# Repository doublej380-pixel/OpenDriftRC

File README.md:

OpenDrift is an open source drift gyro for RC drift cars, built around the Waveshare ESP32-S3 Touch AMOLED 1.64 board. It reads steering, throttle, and optional gain channels from a receiver, mixes driver steering with gyro correction, outputs steering and optional throttle signals, and exposes tuning through both the onboard touch UI and a WiFi web configurator.

OpenDrift v1.0 uses a dedicated selectable-rate control task, a single gyro filter, continuous yaw prediction, throttle-informed load-change prediction, and non-accumulating quiet-drift reference feedback. The goal is to make gyro setup less of a black box while keeping the active control path small enough to reason about.

See the current [Technical Tuning Reference](OpenDrift/docs/Tuning.md) for the setup order, symptom table, surface-profile workflow, and findings from real track testing. The public [tuning guide](https://opendriftrc.com/tuning/) provides the shorter trackside workflow.

Developers and AI assistants can start with the
[project context and handoff](OpenDrift/docs/PROJECT_CONTEXT.md), covering the
development history, architecture, validated findings, safety constraints,
current local work, and deferred investigations. It is a dated summary, not
a verbatim chat archive; verify it against the current source.

## Install Firmware

Visit [opendriftrc.com](https://opendriftrc.com) for the project overview, [wiring reference](https://opendriftrc.com/wiring/), and Open Beta firmware. The [browser installer](https://opendriftrc.com/flash/) provides current AMOLED images with either PWM or CRSF receiver support, without an account, source compilation, or command-line tools. Historical round-display releases remain available but are frozen.

## Current Features

- ESP32-S3 firmware using PlatformIO and Arduino.
- 280 x 456 AMOLED touch UI with swipeable pages and a permanent built-in
  background fallback.
- Up to 16 persistent custom AMOLED backgrounds, selectable from the display
  or web configurator. JPG, PNG, and WebP images can be converted locally at
  [opendriftrc.com/backgrounds](https://opendriftrc.com/backgrounds/).
- Persistent AMOLED theme engine with light/dark text, seven accent palettes,
  and background-aware translucent control panels, based on work contributed
  by [J3vb](https://github.com/J3vb).
- Dedicated 333 Hz IMU/control/steering task isolated from UI, WiFi, and logging work.
- Continuous yaw-acceleration prediction with throttle-informed look-ahead.
- Quiet-drift reference feedback that yields to driver steering and throttle changes.
- Receiver steering input.
- Optional receiver throttle sensing with automatic Performance Mode behavior.
- Receiver gyro gain input.
- Selectable GPIO 18 gyro-gain input or throttle passthrough output.
- Servo output with center, reverse, and travel settings.
- Physical servo endpoint calibration for max left, center, and max right.
- Separate radio steering travel limit.
- Separate servo reverse and gyro reverse.
- Gyro tuning:
  - gain
  - deadband
  - maximum correction
  - smoothing
  - Prediction
  - Countersteer Assist
  - Transition Speed
  - Driver Priority
  - Anti Wobble
- Up to 12 persistent named surface/driving profiles.
- Scrollable trackside profile selection on both displays.
- Do-nothing signal-loss behavior when steering input is lost.
- WiFi access point.
- Browser-based web configurator.
- Non-blocking PSRAM blackbox logging with controller, prediction, throttle, notch, chassis-motion, and correction telemetry.
- Parked blackbox archiving to sequential CSV files on AMOLED microSD, with an
  internal-flash fallback when no card is installed.
- Persistent settings stored in ESP32 preferences.
- Transition Speed adjustment centered at the neutral baseline of `50`.
- Driver Priority adjustment that yields fast direct gyro gain as steering input increases; default `0` preserves the established response.
- Phase-aware Anti Wobble notch with a track-tested default of `50`.
- Separate PWM and full-duplex CRSF targets for Waveshare AMOLED V1 and V2.
- Full-duplex CRSF steering, throttle, gain, link statistics, parameter
  telemetry, neutral failsafes, and [EdgeTX tuning](https://github.com/doublej380-pixel/OpenDriftRC/releases/download/v1.0.8/OpenDrift.lua).
- CRSF channel routing to accessory PWM outputs: GPIO 1–8 on AMOLED V1 and
  GPIO 3–8 on AMOLED V2.

## Hardware Routing

### Supported Boards

The **Waveshare ESP32-S3 Touch AMOLED 1.64** is the final and primary OpenDrift hardware target. New development, UI work, and release testing target this board.

Waveshare ships V1 and V2 revisions that require different firmware. V1 has its version silkscreen at the top of the PCB and uses LCD_CS on GPIO 9. V2 has the silkscreen beside the right-side pin headers and uses LCD_CS on GPIO 46. Select the exact revision in the web flasher.

The older Waveshare 1.28-inch round display build is deprecated and frozen. Its PlatformIO environment and implementation remain in the repository for experimentation, but no new firmware releases or feature-parity work are planned.

AMOLED V1 and the Round board use this PWM pinout:

| Signal | GPIO | Direction | Notes |
| --- | ---: | --- | --- |
| Receiver steering / servo in | 15 | Input | Standard RC PWM input |
| Receiver throttle / throttle in | 16 | Input | Throttle sensing and blackbox input |
| Steering servo / servo out | 17 | Output | Stabilized steering command |
| Gain input / throttle output | 18 | Selectable | Gain-channel input by default, or throttle passthrough output |

GPIO 18 cannot provide throttle output and read receiver gain at the same time.
To keep throttle sensing and gain adjustment, split the receiver throttle
signal to GPIO 16 and the ESC rather than plugging the ESC into OpenDrift.

Make sure the receiver, ESP32 board, and servo power system share ground.

AMOLED V2 keeps receiver steering on GPIO 15 and throttle on GPIO 16, but moves steering output to GPIO 1 and the switchable gain/throttle connection to GPIO 2. Do not use GPIO 17/18 for OpenDrift signals on V2; Waveshare connects those pins to IMU_INT2 and TP_INT.

CRSF targets repurpose the receiver pins:

| Signal | GPIO | Direction | Notes |
| --- | ---: | --- | --- |
| CRSF receiver TX | 17 | Input | Native CRSF channel and link frames |
| CRSF receiver RX | 18 | Output | Full-duplex parameter telemetry |
| Steering servo / servo port | 15 | Output | Fixed 333 Hz servo PWM |
| ESC throttle / throttle port | 16 | Output | Standard 50 Hz ESC PWM with active-neutral failsafe |

AMOLED V2 instead uses GPIO 1 for CRSF RX and GPIO 2 for CRSF TX while retaining GPIO 15 steering-servo output and GPIO 16 ESC output. All CRSF targets use the same full-duplex implementation and the
separate `OpenDriftCRSF` settings namespace and do not overwrite a PWM tune.

CRSF builds can also mirror any receiver channel to accessory outputs from the
WiFi web configurator. AMOLED V1 exposes GPIO 1–8; AMOLED V2 exposes GPIO 3–8
because GPIO 1/2 carry CRSF. Each enabled pin emits standard 50 Hz receiver PWM
and returns to 1500 microseconds when the CRSF link is lost. These are 3.3 V
signal outputs only: power lights and accessories separately and share ground.

Throttle sensing is not required for basic stabilization, but it is strongly recommended. With the throttle signal connected, OpenDrift can release settled-drift features during power changes instead of inferring those events from yaw alone. Treat it like a sensored-motor cable: the fallback works without it, while Performance Mode has substantially better phase awareness.

The servo should be powered from a suitable BEC or ESC receiver rail. Do not rely on the ESP32 board to power a steering servo. A DIY installation must feed the display/development board regulated 5 V, never an unregulated or 6 V-plus BEC output. The OpenDrift daughter boards under development include an onboard regulator. ESP32-S3 GPIOs are 3.3 V signal pins and are not 5 V tolerant.

## Build And Upload

The firmware project is in:

`OpenDrift/`

## Custom AMOLED Backgrounds

OpenDrift keeps the built-in galaxy image in firmware and can additionally
store up to 16 user backgrounds in the board's FFat partition. Custom images
must be 456 x 280 raw RGB565 files; the browser-based
[background converter](https://opendriftrc.com/backgrounds/) creates the exact
format locally from JPG, PNG, or WebP files.

To install one, join the gyro's `OpenDrift` WiFi network, open
`http://192.168.4.1`, and use the **AMOLED Backgrounds** card. Uploaded images
can be selected or deleted there, and can also be selected from the
**Backgrounds** page on the AMOLED display. Keep the car stationary while an
image is being written to flash. Leaving the selection on **Built-in** uses the
factory background and consumes no additional storage.

Build with PlatformIO:

```sh
pio run
```

The default environment is `waveshare_amoled_164`. Build or upload it explicitly with:

```sh
pio run -e waveshare_amoled_164
pio run -e waveshare_amoled_164 -t upload
```

The custom PlatformIO board definition is included at `OpenDrift/boards/waveshare_amoled_164.json`.

AMOLED V2 uses separate targets:

```sh
pio run -e waveshare_amoled_164_v2
pio run -e waveshare_amoled_164_v2_crsf
```

CRSF builds are intentionally separate:

```sh
pio run -e waveshare_amoled_164_crsf
```

Both supported targets enable full-duplex CRSF, GPIO 16 ESC output, and neutral-hold arming. Telemetry uses GPIO 18 on AMOLED V1 and GPIO 2 on AMOLED V2.

Main dependencies are managed in `OpenDrift/platformio.ini`:

- SensorLib
- LovyanGFX
- ESP32Servo

## First Power-On

On boot, OpenDrift initializes:

1. Display
2. Settings
3. IMU
4. Servo output
5. Receiver inputs
6. Touch
7. Gyro calibration
8. WiFi, if enabled
9. UI

Keep the car still during startup so gyro calibration can capture a clean yaw-rate offset.

## Onboard UI Pages

Swipe left/right to move between pages.

### Main

Shows the current gyro gain and provides:

- `- / +`: adjust stored gain when radio gain input is not overriding it.
- `CAL`: recalibrate gyro offset. Use this when the car is sitting still and the gyro seems biased.

### Core

Primary correction limits:

- `Deadband`: yaw-rate zone ignored around zero.
- `MAX CORRECTION`: maximum gyro movement across the full calibrated endpoint-to-endpoint steering span. `50%` equals center-to-endpoint authority; `100%` can override one endpoint to the other.
- `GYRO REV`: reverses only the gyro correction direction.

Use `GYRO REV` when normal steering direction is correct, but the gyro counter-steers the wrong way.

### Response

Fast controller behavior:

- `SMOOTHING`: the optional software yaw low-pass; defaults to `0.00` (bypass).
- QMI8658 gyro hardware LPF is bypassed; its selector is retired.
- `PREDICTION`: continuous yaw-acceleration look-ahead.

### Assistance

Slow quiet-drift behavior:

- `COUNTERSTEER`: chooses how much additional steady countersteer OpenDrift carries. Zero preserves the driver-led base response; higher values reduce the steering load on the driver without increasing fast yaw damping.
Hold Assist, Drift Memory, and Memory Limit are retired on non-MPU6050 builds.
Old saved values and profiles cannot reactivate them. The experimental MPU6050
targets retain their original controls, defaults, and 20/98/256 Hz filter choices.

### Tail Response

`TAIL SPEED` is tuned separately from the core v1.0 controls:

- `50` is the Open Beta baseline response.
- Below `50` adds damping during deliberate entries and transitions.
- Above `50` releases some damping so the chassis can rotate faster.
- The effect is reduced in a settled drift and cannot reverse gyro correction.

Keep it at `50` unless deliberately collecting same-car experimental A/B data.

`SMOOTH` is intentionally inverted from raw filter math: higher numbers mean more smoothing and slower gyro response.

Deadband is applied as a soft deadband. Small yaw noise is still ignored, but correction fades in from zero instead of jumping as soon as yaw crosses the deadband value.

Conservative first-power values:

| Setting | Start |
| --- | ---: |
| Gain | 1.50 |
| Deadband | 4.0 |
| Max correction | 100% |
| Smoothing | 0.00 |
| Countersteer Assist | 100 |
| Driver Priority | 0 |
| Prediction | 0 |

Tune symptoms:

| Symptom | Try |
| --- | --- |
| Weaves left/right driving straight | Increase deadband or lower gain |
| Initial response is strong but runs out of authority | Raise Max Correction carefully |
| Fast response overshoots | Add Prediction in steps of 5 |
| Prediction makes transitions nervous | Lower Prediction |
| Car is stable but the driver carries too much countersteer | Raise Countersteer Assist in steps of 10 |
| Gyro feels too hands-on during a settled drift | Lower Countersteer Assist |
| High gain feels restrictive near full steering | Add Driver Priority in steps of 5; start below 20 |
| Mid-drift wheel oscillation | Lower gain first; verify servo and chassis |
| Feels slow or lazy | Lower smoothing slightly or raise gain |

### Radio

Live receiver monitor:

- Steering pulse and signal state.
- Gain pulse and signal state.
- Current gain value.
- Calibration values.
- Position bars for steering and gain.

Use this page to confirm the receiver is connected and moving through a sensible range.

In a CRSF build the monitor shows channel 1 steering, channel 2 throttle, and
channel 3 gain decoded from the digital link.

### Steering

Steering output setup:

- `TRV`: scales driver steering input without reducing gyro correction authority.
- `REV`: reverses physical servo direction.
- Swipe once more to open the dedicated **Physical Endpoints** page.

### Physical Servo Endpoints

The calibration page uses three large capture buttons. Each button starts red
and turns green after it has captured the servo's actual physical PWM position:

- `MAX LEFT`: position the wheels at their safe physical left stop, then capture it.
- `CENTER`: capture the transmitter at neutral.
- `MAX RIGHT`: position the wheels at their safe physical right stop, then capture it.

OpenDrift saves the calibration after all three physical positions are captured
on opposite sides of center. The saved endpoints become the final asymmetric
servo map and hard clamp, so neither the driver nor gyro can push through them.

CRSF users can perform the same three captures from the EdgeTX `OpenDrift.lua`
tool. Calibration state is persistent and shared: completing it on the radio
turns the AMOLED buttons green, while completing it on the display updates the
radio's `Endpoints` status to `YES`.

Suggested calibration flow:

1. Set servo direction first, then use steering/transmitter endpoint adjustment to position the wheels at the safe physical left stop and tap `MAX LEFT`.
2. Release steering to neutral and tap `CENTER`.
3. Position the wheels at the safe physical right stop and tap `MAX RIGHT`.
4. Confirm all three buttons are green and the page says `SAVED - TAP TO RESET`.
5. Return to Steering and verify the wheels remain inside both saved physical stops.

Changing `REV`, Servo Center, or Servo Travel after calibration deliberately
clears the saved calibration because those changes alter the physical output map.

Servo reverse and gyro reverse are separate on purpose:

- Use `REV` on the Steering page when driver steering moves the wheels backward.
- Use `GYRO REV` on the Gyro page when driver steering is correct but gyro correction is backward.

Physical endpoint calibration and steering travel are separate on purpose:

- Use `MAX LEFT`, `CENTER`, and `MAX RIGHT` to set the servo's physical output limits.
- Use `TRV` to scale driver steering without reducing gyro authority.
- Use Max Correction to select how much of the calibrated physical range the gyro may command.

### WiFi

Shows WiFi state and connected client count.

AMOLED development builds default to **WiFi off** on fresh installs and factory
reset. Turn it on from this page when needed. Existing saved boot preferences
are preserved; change "Enable WiFi on boot" in the web configurator if desired.
When off, the radio driver is stopped/deinitialized, mDNS is stopped, and the
HTTP client/listener closes. Health checks and HTTP request polling do not run.
The small route table and shared networking framework allocations can remain
in memory; "off" does not mean the firmware has zero networking-related RAM.

- `WIFI ON/OFF`: toggles the access point.

When WiFi is enabled, connect to the `OpenDrift` network and open:

`http://192.168.4.1/`

### System

Basic firmware/system information. Tap the GPIO 18 mode button to switch between `GAIN INPUT` and `THROTTLE OUT`.

### Profiles

The Profiles page lists the driving profiles created in the web configurator. Tap a profile to activate its complete driving tune. Swipe vertically when more than four profiles exist; the list supports up to 12 profiles.

Profiles save gain, deadband, max correction, smoothing, Prediction, Countersteer Assist, Driver Priority, and radio steering travel. Retired fields remain reserved for compatibility but are forced off on non-MPU6050 builds. Trackside adjustments automatically save back to the active profile.

Hardware and installation settings remain global, including gyro/servo direction, physical steering endpoints, servo center and travel, WiFi, logging, and GPIO mode. Switching surfaces therefore cannot disturb the car's physical setup.

### Control and servo rate

Current development firmware uses **333 Hz only** for steering/control, with an approximately 3 ms interval. **Use only a servo explicitly rated for 333 Hz.** Digital does not automatically mean compatible; an unsupported update rate can cause heat, buzzing, erratic steering, or servo damage. Existing 250 Hz settings migrate to 333 Hz on installation.

The screen and web configurator show the fixed rate; there is no rate selector in the radio menu. Throttle output retains its independent 50/250/333 Hz setting and is not forced to the steering rate.

## Web Configurator

When WiFi is enabled, OpenDrift starts a web configurator at:

`http://192.168.4.1/`

Current web settings:

- Create named driving profiles from the current tune
- Activate or delete existing profiles
- Gyro gain
- Channel 3 gain minimum / maximum (`0.00-6.00`)
- Deadband
- Reverse gyro correction
- Max correction
- Smoothing
- Prediction strength
- Transition Speed
- Driver Priority
- Anti Wobble
- Servo reverse
- Servo center
- Servo travel
- Steering max left / center / max right
- Radio steering travel
- Gain channel low / high
- GPIO 18 gain-input or throttle-output mode
- WiFi enabled on boot
- WiFi auto-off timeout
- Blackbox logging enabled
- Raw pitch, roll, acceleration, and surface-disturbance telemetry for chassis analysis

The web page also shows the active profile, live receiver pulse values for steering, throttle, and gain, plus the active GPIO 18 mode.

Use the web configurator when you want to make several changes quickly. Use the onboard UI when tuning trackside without a phone or laptop.

## Onboard Blackbox Log

OpenDrift records fixed-size blackbox samples into a 4 MB circular PSRAM buffer at about 20 Hz while steering receiver signal is present.

Blackbox logging is disabled by default. Enable `Onboard logging` in the web configurator only when you want to collect data, then save settings.

No flash or filesystem writes occur while driving. Once the circular buffer is
full, the oldest records are overwritten so the newest behavior remains
available. Park the car before saving the RAM log to persistent storage.

On AMOLED hardware, an installed microSD card is preferred and each dump is
saved as a new CSV (`opendrift-blackbox-0001.csv`, `0002`, and onward). Existing
sessions are preserved and numbering continues after reboot. Without an SD
card, OpenDrift stores one compact binary archive in internal flash and converts
it to CSV when downloaded through the web configurator.

The dedicated AMOLED **Blackbox** page shows the current RAM records, used and
available space, captured duration, archive destination, saved-log statistics,
and dump progress. It also provides logging, dump, and RAM-clear controls.

For acquisition/wobble testing, the web configurator's **Control diagnostics**
card captures up to 45 seconds at control-loop rate. Start it before driving.
With an SD card, the ordinary dump action also saves a matching numbered
`opendrift-diagnostics-0001.csv` beside the blackbox CSV. Wait until dump
completion before powering off. Without SD, download the timing CSV over WiFi
before restarting; internal-flash dumps do not include this RAM-only capture.
See [IMU diagnostics](OpenDrift/docs/IMU_DIAGNOSTICS.md) and
[screen performance testing](OpenDrift/docs/SCREEN_PERFORMANCE.md).

### AMOLED USB maintenance and boot recovery

All AMOLED V1/V2 PWM/CRSF builds, including the private GPIO8 target, support
USB maintenance. **No SD card is required for firmware updates.** Hold **USB
MODE** on the System page for 1.5 seconds while parked. The board restarts into
an isolated mode with steering, throttle, and controller tasks inactive.
Connect a data-capable USB cable and copy the correct build's application
`firmware.bin` onto the firmware-update drive. Wait for **Update Complete**
and automatic reboot; do not disconnect during writing. An inserted SD card
appears separately as a read-only log drive. The maintenance restart button
disconnects the volumes before returning to normal operation.

The SD-ready indication reports device-side readiness, not completion of the
computer's filesystem mount. USB SD reads now use up to the existing 4 KB
buffer with event-driven completion instead of per-sector polling. See
[USB SD performance testing](OpenDrift/docs/USB_SD_PERFORMANCE.md) if the
drive appears but takes a long time to open; hardware validation is still
required to measure the improvement.

For official builds previously using the single-app partition layout, install
the full factory image once through the webflasher or perform a normal full
PlatformIO upload: an app-only USB update
cannot install a new partition table. The new layout keeps NVS and FFat at
their existing addresses, but back up your tune/logs before upgrading. USB
serial ports may re-enumerate after the switch to native TinyUSB. Do not erase
the whole chip as part of the normal upgrade.

After three consecutive unfinished boots across software/watchdog resets,
the next boot enters USB recovery before the IMU, outputs, and controller are
started. Automatic recovery skips SD mounting so a bad card cannot block the
updater. Successful normal startup clears the RTC failure audit after 15
seconds. Intentional USB-mode changes are excluded. Cold power loss/brownout
starts a fresh audit; corrupt apps/bootloaders still require hardware BOOT
recovery. The headless private Matrix builds retain their existing USB serial
configuration; this AMOLED maintenance interface is not enabled on Matrix.

The web configurator shows the current log size and provides:

- `Download CSV`
- `Clear RAM Log`
- `Dump RAM Log to SD card` or internal flash, according to available storage
- `Download saved CSV`

Log rows include:

- Time
- Raw yaw rate
- Filtered yaw rate
- Roll and pitch gyro rates (`gyro_x_dps`, `gyro_y_dps`)
- Raw X/Y/Z acceleration in g
- Total acceleration magnitude and high-frequency acceleration delta
- A filtered `surface_disturbance` score from `0.0` to `1.0`
- Requested gyro correction before Max Correction
- Limited gyro correction after Max Correction
- Applied gyro correction after the driver/gyro steering mix
- Correction saturation state
- Steering input and calibrated steering command
- Servo output
- Reserved Servo Quiet field (zero; command suppression is retired)
- Throttle input
- Gain input and active gain
- Active deadband, max correction, smoothing, Prediction, Countersteer Assist, and Driver Priority (retired memory/hold fields remain zero for CSV compatibility)
- Driver Priority scale and effective live direct gain
- Predicted yaw, quiet-drift reference, reference error, steady countersteer contribution, and memory correction
- Driver steering activity and throttle-prediction blend
- Controller phase (`0` idle, `1` entry, `2` settled, `3` transition) and reference-lock blend
- Anti Wobble notch depth, isolated residual, tracked notch frequency, transition-authority blend, and throttle-lift blend
- Steering/throttle/gain signal state and GPIO 18 mode

Suggested test workflow:

1. Connect to the `OpenDrift` WiFi network.
2. Open `http://192.168.4.1/`.
3. Enable onboard logging if it is off, then save settings.
4. Tap `Clear RAM Log`.
5. Drive the car.
6. Stop and leave the car parked for two seconds.
7. Dump the RAM log from the AMOLED Blackbox page, EdgeTX tool, or web
   configurator.
8. Download the saved CSV over WiFi, or remove/read the SD card later.

The CSV can be pasted into a spreadsheet or plotted to see whether the car spun because of delayed correction, overcorrection, max correction saturation, noisy yaw, or steering/radio behavior.

`surface_disturbance` still combines sudden acceleration-vector changes, roll/pitch rate, and low-g unloading indicators for analysis. OpenDrift v1.0 logs it but does not currently apply terrain correction.

## Gyro Algorithm Overview

Current development firmware runs this path at the fixed 333 Hz rate:

1. Read receiver steering, throttle, and IMU yaw.
2. Subtract calibrated gyro offset and apply soft deadband.
3. Bypass QMI gyro hardware LPF and apply optional software yaw low-pass.
4. Estimate short-horizon yaw from filtered yaw acceleration.
5. Extend that horizon when throttle predicts application or a longer off-throttle load change.
6. Shape damping briefly during deliberate direction changes without changing the hard correction ceiling.
7. Apply the phase-aware Anti Wobble notch around the tracked 2.5-3.6 Hz wheel-resonance band while preserving slow chassis yaw and useful response outside that band.
8. Convert predicted yaw directly into correction with Gain.
9. Learn a slow yaw reference while driver steering and throttle are quiet.
10. Add optional Countersteer Assist from the slow learned reference only.
11. Limit signed gyro movement to the configured full-span Max Correction
    percentage, then mix it with driver steering and clamp the combined command.
12. Apply the calibrated physical endpoint map as the final hard servo limit.

Driver steering activity and throttle changes make the slow reference yield
immediately. Neither disables the fast direct damping path.

## Signal Loss Behavior

Current CRSF development builds also require [CH4 arming](OpenDrift/docs/ARMING.md).
CH4 low holds steering centered and throttle neutral with the screen usable;
CH4 high requests drive after a neutral hold and sleeps the AMOLED/UI. Physical
endpoint capture/reset is unavailable under the selected strict parked lock.
Read the bench checklist before installing this development firmware.

The standard PWM builds retain the existing do-nothing behavior: if steering
input disappears, OpenDrift does not send a new servo command.

This leaves the servo at the last commanded position. It is intentionally a simple do-nothing behavior while failsafe strategy is still being evaluated.

The full CRSF build has deterministic behavior because all channels share one
link state. A channel frame older than 50 ms centers steering and commands
neutral throttle. Throttle remains locked until a valid link has held neutral
for 500 ms after boot or reconnection.

## Tuning

Use the [Technical Tuning Reference](OpenDrift/docs/Tuning.md) rather than tuning every setting at once. The most important lessons from development are:

- Establish a mechanically sound car before blaming the gyro.
- Set the servo's internal anti-wobble only as high as it can run without buzzing; high servo torque/power can amplify internal oscillation.
- Treat Gain as the primary surface-dependent setting and store each surface in a profile.
- Tune entries with Gain, Max Correction, and optional Smoothing.
- Add Prediction in small steps only after the direct response is understood.
- Use Countersteer Assist to choose driver-led versus gyro-led settled drifts without retuning Gain.
- Connect throttle sensing so OpenDrift can anticipate power and load changes.

OpenDrift v1.0 is the first public controller. Start from the conservative
values in the tuning reference and save proven surface setups as profiles.

## Future Work

- **Servo resonance calibration:** add a stationary calibration mode that sweeps a small steering command across a safe frequency range and captures high-rate chassis IMU data. Because the servo is rigidly mounted to the chassis, its buzz and self-oscillation should be measurable without another sensor. The first version should compare vibration energy, dominant resonances, settling, and left/right behavior to help evaluate internal servo anti-wobble, torque, power, and response settings and recommend OpenDrift quiet-band and correction-rate settings. Command shaping or resonance compensation should only follow after repeatable measurements show that it can reduce vibration without adding harmful control-loop delay.

## Project Layout

Important folders:

- `OpenDrift/src/main.cpp`: main firmware loop and control mixing.
- `OpenDrift/lib/GyroController`: gyro filtering and correction generation.
- `OpenDrift/lib/RadioInput`: receiver PWM input capture.
- `OpenDrift/lib/CrsfInput`: bounded native CRSF frame decoding and telemetry.
- `OpenDrift/lib/CrsfParameterDevice`: bidirectional CRSF settings device.
- `OpenDrift/lib/EscOutput`: dedicated 50 Hz LEDC throttle output.
- `OpenDrift/lib/Servo`: servo output wrapper.
- `OpenDrift/lib/Settings`: persistent settings.
- `OpenDrift/lib/UI`: onboard touch UI.
- `OpenDrift/lib/WebConfigurator`: web settings page.
- `OpenDrift/lib/WIFIManager`: WiFi access point control.
- `OpenDrift/lib/Backgrounds`: persistent AMOLED background storage and
  recovery.
- `OpenDrift/docs/Tuning.md`: complete tuning and blackbox interpretation guide.
- `OpenDrift/docs/CRSF-Experimental.md`: CRSF wiring, failsafes, and validation
  workflow.
- `OpenDrift/radio/edgetx`: source for the [OpenDrift EdgeTX tuning tool](https://github.com/doublej380-pixel/OpenDriftRC/releases/download/v1.0.8/OpenDrift.lua).
- `OpenDrift/assets/backgrounds`: built-in AMOLED fallback background data.
- `OpenDrift/boards`: custom PlatformIO board definitions.

## License

See `LICENSE`.

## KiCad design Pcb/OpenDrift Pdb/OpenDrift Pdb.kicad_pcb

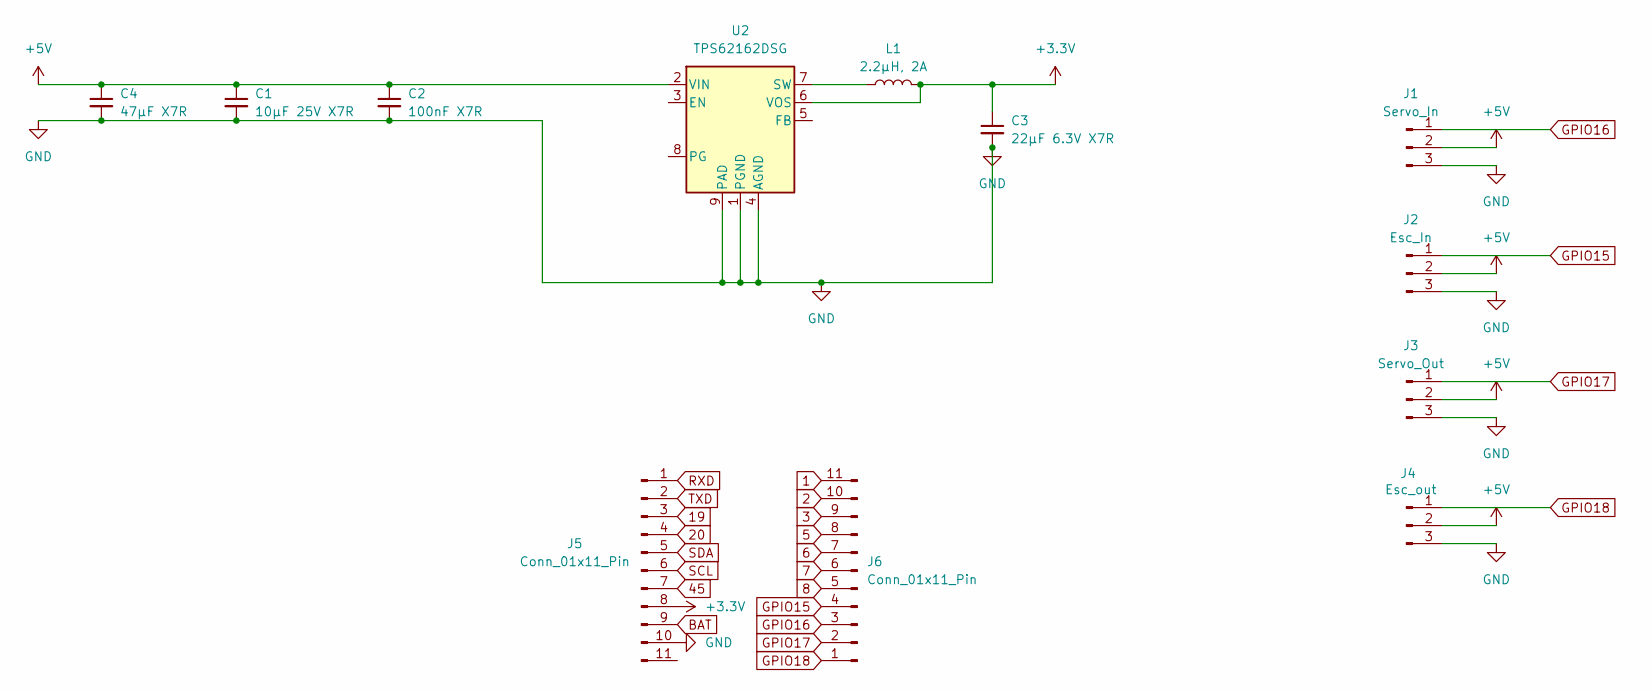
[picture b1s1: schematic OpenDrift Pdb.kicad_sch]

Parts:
C1: 10µF 25V X7R; C_0805_2012Metric
C2: 100nF X7R; C_0603_1608Metric
C3: 22µF 6.3V X7R; C_0805_2012Metric
C4: 47µF X7R; C_0805_2012Metric
J1: Servo_In; JST_PH_S3B-PH-K_1x03_P2.00mm_Horizontal
J2: Esc_In; JST_PH_S3B-PH-K_1x03_P2.00mm_Horizontal
J3: Servo_Out; JST_PH_S3B-PH-K_1x03_P2.00mm_Horizontal
J4: Esc_out; JST_PH_S3B-PH-K_1x03_P2.00mm_Horizontal
J5, J6: Conn_01x11_Pin; PinHeader_1x11_P2.54mm_Vertical
L1: 2.2µH, 2A; L_Coilcraft_XAL4020-XXX
U2: TPS62162DSG; WSON-8-1EP_2x2mm_P0.5mm_EP0.9x1.6mm_ThermalVias

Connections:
1: J6.11
2: J6.10
3: J6.9
5: J6.8
6: J6.7
7: J6.6
8: J6.5
19: J5.3
20: J5.4
45: J5.7
+3.3V: C3.1, J5.8, L1.2, U2.6 (VOS)
+5V: C1.1, C2.1, C4.1, J1.2, J2.2, J3.2, J4.2, U2.2 (VIN)
BAT: J5.9
GND: C1.2, C2.2, C3.2, C4.2, J1.3, J2.3, J3.3, J4.3, J5.10, U2.1 (PGND), U2.4 (AGND), U2.9 (PAD)
GPIO15: J2.1, J6.4
GPIO16: J1.1, J6.3
GPIO17: J3.1, J6.2
GPIO18: J4.1, J6.1
unnamed: L1.1, U2.7 (SW)
RXD: J5.1
SCL: J5.6
SDA: J5.5
TXD: J5.2

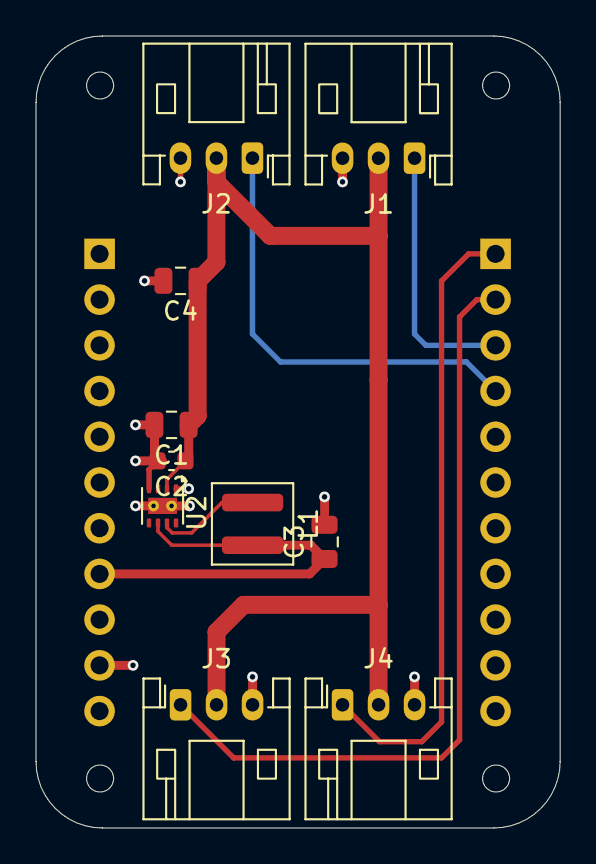
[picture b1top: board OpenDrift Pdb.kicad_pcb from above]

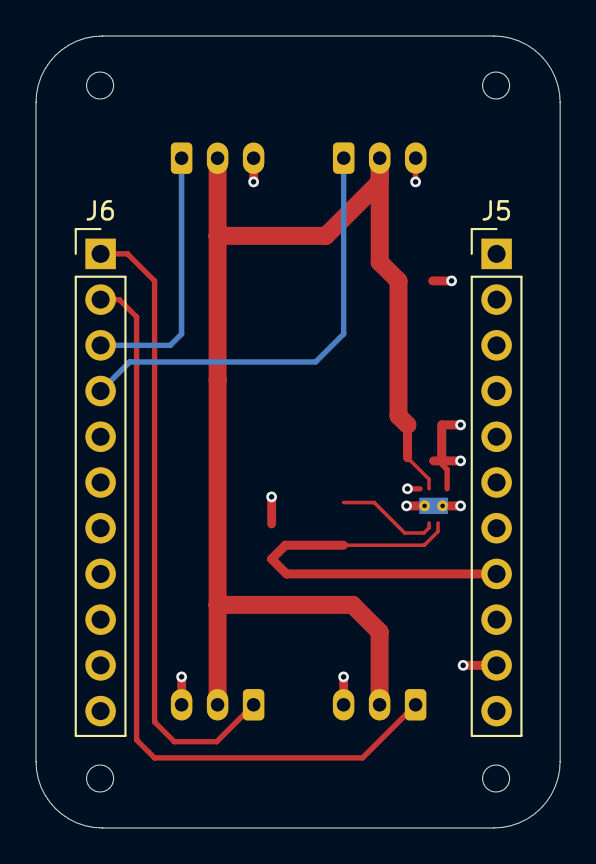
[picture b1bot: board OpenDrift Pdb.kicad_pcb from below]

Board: 4 copper layers, 29.1 x 44.0 mm, 12 parts (2 on the bottom side), 8 nets.

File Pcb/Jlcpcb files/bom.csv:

Designator,Footprint,Quantity,Value,LCSC Part #
C1,0805,1,10µF 25V X7R,
C2,0603,1,100nF X7R,
C3,0805,1,22µF 6.3V X7R,
C4,0805,1,47µF X7R,
J1,JST_PH_S3B-PH-K_1x03_P2.00mm_Horizontal,1,Servo_In,
J2,JST_PH_S3B-PH-K_1x03_P2.00mm_Horizontal,1,Esc_In,
J3,JST_PH_S3B-PH-K_1x03_P2.00mm_Horizontal,1,Servo_Out,
J4,JST_PH_S3B-PH-K_1x03_P2.00mm_Horizontal,1,Esc_out,
"J5, J6",PinHeader_1x11_P2.54mm_Vertical,2,Conn_01x11_Pin,
L1,L_Coilcraft_XAL4020-XXX,1,"2.2µH, 2A",
U2,WSON-8-1EP_2x2mm_P0.5mm_EP0.9x1.6mm_ThermalVias,1,TPS62162DSG,
